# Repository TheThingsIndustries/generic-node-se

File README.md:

# Generic Node Sensor Edition (GNSE)

## About

LoRaWAN promised you roaming, secure and low-cost sensors that last on a battery for years. _Generic Node_ platform delivers this promise with additional strong end to end encryption and firmware over the air update in a device with multiple sensors that can be configured and programmed to support many use cases.

This repository contains all the necessary hardware and software files for the GNSE LoRaWAN node. The core of the system is based off the STM32WL55xx dual-core LoRaWAN SOC.

## Specification
- [STM32WL55CCU6](https://www.st.com/en/microcontrollers-microprocessors/stm32wl-series.html) dual-core Arm Cortex®-M4/M0+ @48 MHz
- 256 Kbytes of Flash & 64 Kbytes of SRAM
- SX126x sub-GHz radio
- Power output up to +22.00 dBm
- LoRa, (G)FSK, (G)MSK, BPSK modulations
- 868 MHz & 915 MHz dual-band operation
- 2xAA battery powered node with wide input voltage range: 2.2V - 5.5V
- [ATECC608A-TNGLORA](https://www.microchip.com/wwwproducts/en/ATECC608A-TNGLORA) pre-provisioned LoRaWAN secure element
- [LIS2DH12](https://www.st.com/en/mems-and-sensors/lis2dh12.html) - ULP 3-axis accelerometer
- [SHTC3](https://www.sensirion.com/en/environmental-sensors/humidity-sensors/digital-humidity-sensor-shtc3-our-new-standard-for-consumer-electronics/) humidity and temperature sensor
- [MX25R1635](https://www.macronix.com/en-us/products/NOR-Flash/Serial-NOR-Flash/Pages/default.aspx) 16Mb SPI NOR Flash for FUOTA and data-logging
- A user button, an RGB LED, a buzzer and a user-friendly expansion and programming options.

## Development

The necessary schematics and the PCB files can be found in [Hardware](./Hardware).

Software libraries and sample applications can be found in [Software](./Software).

## Documentation

The [Generic Node documentation website](https://www.genericnode.com/docs/) provides information about the node hardware and software features.

## Contribution

Our [contribution guideline](./CONTRIBUTING.md) provides more information on how to assist us with the development of GNSE.

## Legal

[Generic Node license terms and conditions](./LICENSE.md) apply.

[Contact The Things Industries](https://thethingsindustries.com/contact/) for licensing.

Copyright © 2021 The Things Industries B.V.

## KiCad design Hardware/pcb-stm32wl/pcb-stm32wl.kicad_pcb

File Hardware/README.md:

# GNSE Hardware
The reference design hardware provides the needed resources for device production, and the design can be tailored to serve a specific use case.

## Structure

- [sch](./sch/) folder contains the schematics files
- [lib](./lib/) folder contains [KiCad](https://kicad.org/) design libraries
- [pcb-stm32wl](./pcb-stm32wl/) folder contains the layout of the core STM32WL PCB
- [pcb-bolink-batteryHolder](./pcb-bolink-batteryHolder/) folder contains the layout of the bolink enclosure battery holder PCB
- [fab](./fab/) contains fabrication related files such as bill of materials(bom) and gerber files

> Please [contact The Things Industries](https://thethingsindustries.com/contact/) for the latest HW fabrication files

## Documentation

The [Generic Node documentation website](https://www.genericnode.com/docs/) provides information about the hardware features and how to [get started with the hardware development](https://www.genericnode.com/docs/getting-started/se-hw/).

## Legal
Copyright © 2021 The Things Industries B.V.

[Contact The Things Industries](https://thethingsindustries.com/contact/) for licensing.

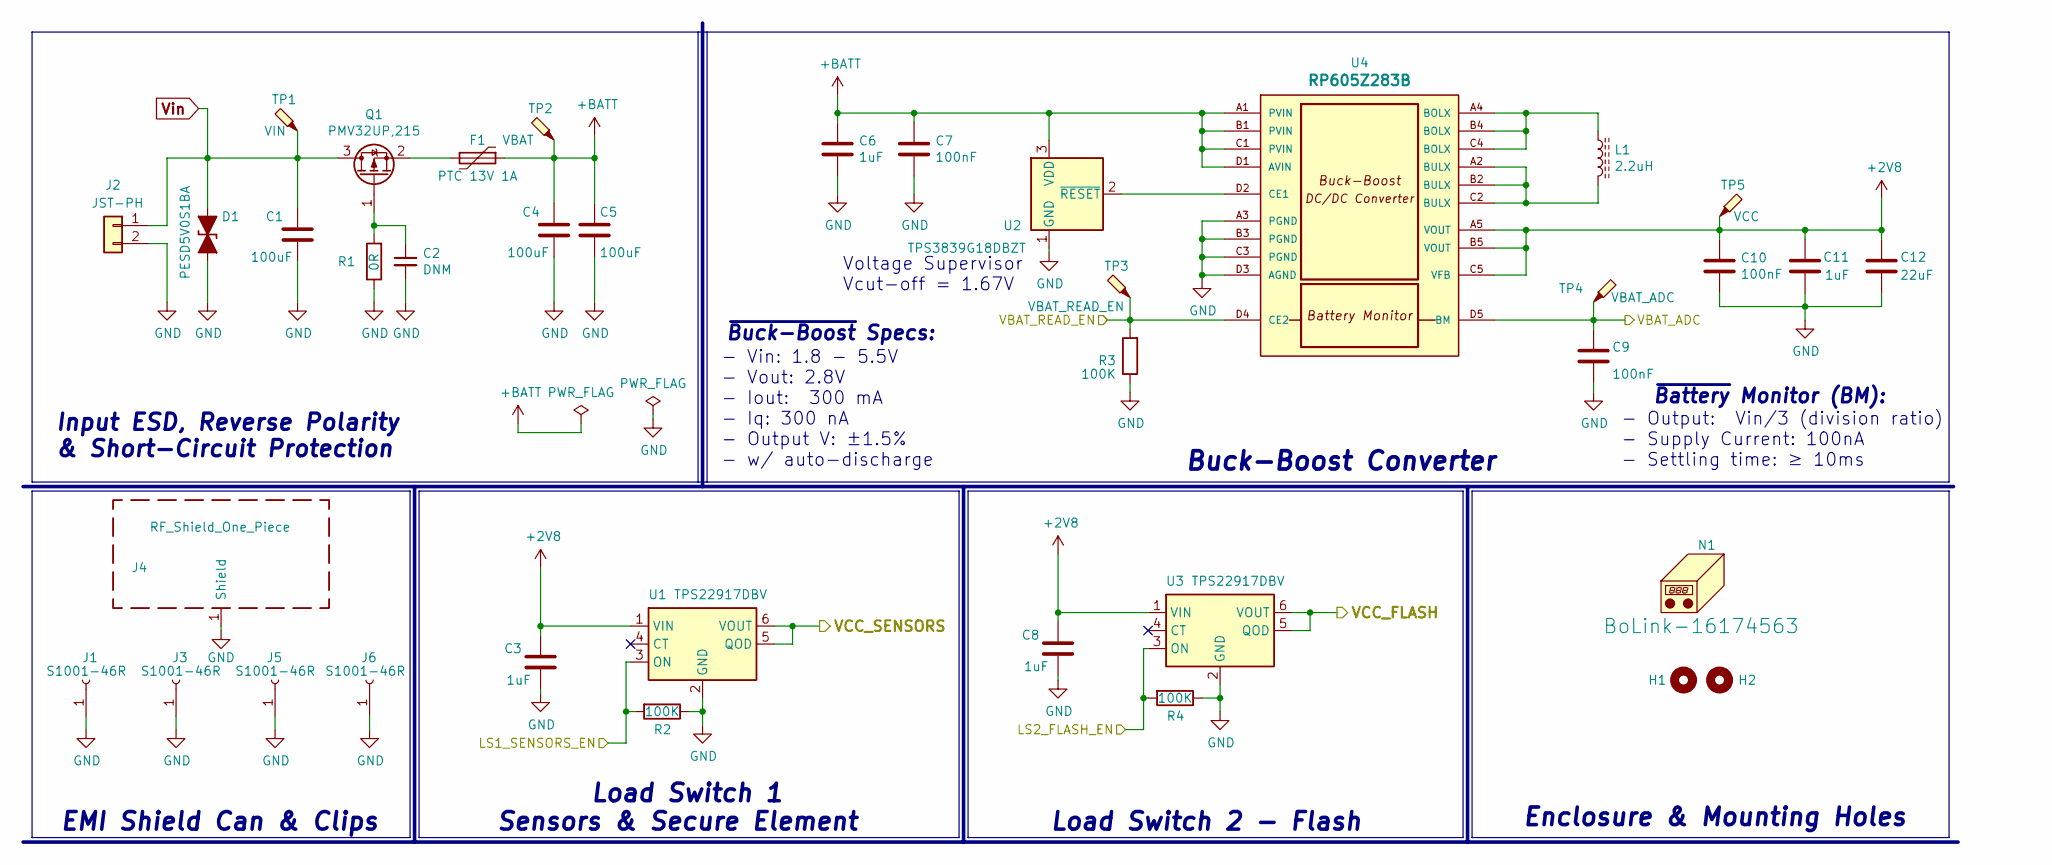
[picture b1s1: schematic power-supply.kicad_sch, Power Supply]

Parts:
C1, C4, C5: 100uF; C_1206_3216Metric; MPN JMK316ABJ107ML-T
C2: DNM; C_0402_1005Metric; MPN CC0402KRX7R7BB103
C3, C6, C8, C11: 1uF; C_0402_1005Metric; MPN CL05A105KQ5NNNC
C7, C9, C10: 100nF; C_0402_1005Metric; MPN CC0402KRX7R7BB104
C12: 22uF; C_0603_1608Metric; MPN CC0603MRX5R5BB226
D1: PESD5V0S1BA; D_SOD-323; MPN PESD5V0S1BA,115
F1: PTC 13V 1A; Fuse_1210_3225Metric_Castellated; MPN SMD1210-050
H1, H2: MountingHole; MountingHole_2.5mm
J1, J3, J5, J6: S1001-46R; RF_Shield_Clip_S1001-46R; MPN DNM
J2: JST-PH; JST_PH_B2B-PH-SM4-TB_1x02-1MP_P2.00mm_Vertical; MPN B2B-PH-SM4-TB(LF)(SN)
J4: RF_Shield_One_Piece; RF_Shield_SnapOn_30x20mm_w_Cutout_n_GND_Pads; MPN DNM
L1: 2.2uH; L_HPC4012TF-2R2M; MPN HPC4012TF-2R2M
N1: BoLink-16174563; BoLink_704025; MPN DNM
Q1: PMV32UP,215; SOT-23; MPN PMV32UP,215
R1: 0R; R_0402_1005Metric; MPN RC0402FR-070RL
R2, R3, R4: 100K; R_0402_1005Metric; MPN RC0402FR-07100KL
TP1: VIN; TestPoint_Pad_D1.5mm; MPN DNM
TP2: VBAT; TestPoint_Pad_D1.5mm; MPN DNM
TP3: VBAT_READ_EN; TestPoint_Pad_D1.5mm; MPN DNM
TP4: VBAT_ADC; TestPoint_Pad_D1.5mm; MPN DNM
TP5: VCC; TestPoint_Pad_D1.5mm; MPN DNM
U1, U3: TPS22917DBV; SOT-23-6; MPN TPS22917DBVR
U2: TPS3839G18DBZT‎; SOT-23; MPN TPS3839G18DBZT‎
U4: RP605Z283B; WLCSP-20-P3_1.994x1.609mm_Layout5x4_P0.4mm; MPN RP605Z283B-E2-F

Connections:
+BATT: C4.2, C5.2, C6.1, C7.1, F1.1, TP2.1, U2.3 (VDD), U4.A1 (PVIN), U4.B1 (PVIN), U4.C1 (PVIN), U4.D1 (AVIN)
/LoRa MCU/PB2: C9.1, TP4.1, U4.D5 (BM); also elsewhere on the board
/LoRa MCU/PB4: R3.2, TP3.1, U4.D4 (CE2); also elsewhere on the board
/Peripherals/VCC_FLASH: U3.5 (QOD), U3.6 (VOUT); also elsewhere on the board
/Peripherals/VCC_SENSORS: U1.5 (QOD), U1.6 (VOUT); also elsewhere on the board
/Power Supply/LS1_SENSORS_EN: R2.2, U1.3 (ON); also elsewhere on the board
/Power Supply/LS2_FLASH_EN: R4.2, U3.3 (ON); also elsewhere on the board
GND: C1.1, C2.2, C3.2, C4.1, C5.1, C6.2, C7.2, C8.2, C9.2, C10.1, C11.2, C12.1, D1.2 (A2), J1.1, J2.2, J3.1, J4.1, J5.1, J6.1, R1.1, R2.1, R3.1, R4.1, U1.2 (GND), U2.1 (GND), U3.2 (GND), U4.A3 (PGND), U4.B3 (PGND), U4.C3 (PGND), U4.D3 (AGND); also elsewhere on the board
unnamed: C2.1, Q1.1 (G), R1.2
unnamed: F1.2, Q1.2 (S)
unnamed: L1.1, U4.A4 (BOLX), U4.B4 (BOLX), U4.C4 (BOLX)
unnamed: L1.2, U4.A2 (BULX), U4.B2 (BULX), U4.C2 (BULX)
unnamed: U2.2 (~RESET), U4.D2 (CE1)
VDDRF: C3.1, C8.1, C10.2, C11.1, C12.2, TP5.1, U1.1 (VIN), U3.1 (VIN), U4.A5 (VOUT), U4.B5 (VOUT), U4.C5 (VFB); also elsewhere on the board
Vin: C1.2, D1.1 (A1), J2.1, Q1.3 (D), TP1.1; also elsewhere on the board

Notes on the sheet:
- Output: Vin/3 (division ratio) - Supply Current: 100nA - Settling time: ≥ 10ms
Buck-Boost Converter
EMI Shield Can & Clips
~{Buck-Boost} Specs:
- Vin: 1.8 - 5.5V - Vout: 2.8V - Iout: 300 mA - Iq: 300 nA - Output V: ±1.5% - w/ auto-discharge
Load Switch 1 Sensors & Secure Element
Load Switch 2 - Flash
Enclosure & Mounting Holes
Voltage Supervisor Vcut-off = 1.67V
~{Battery} Monitor (BM):
Input ESD, Reverse Polarity & Short-Circuit Protection

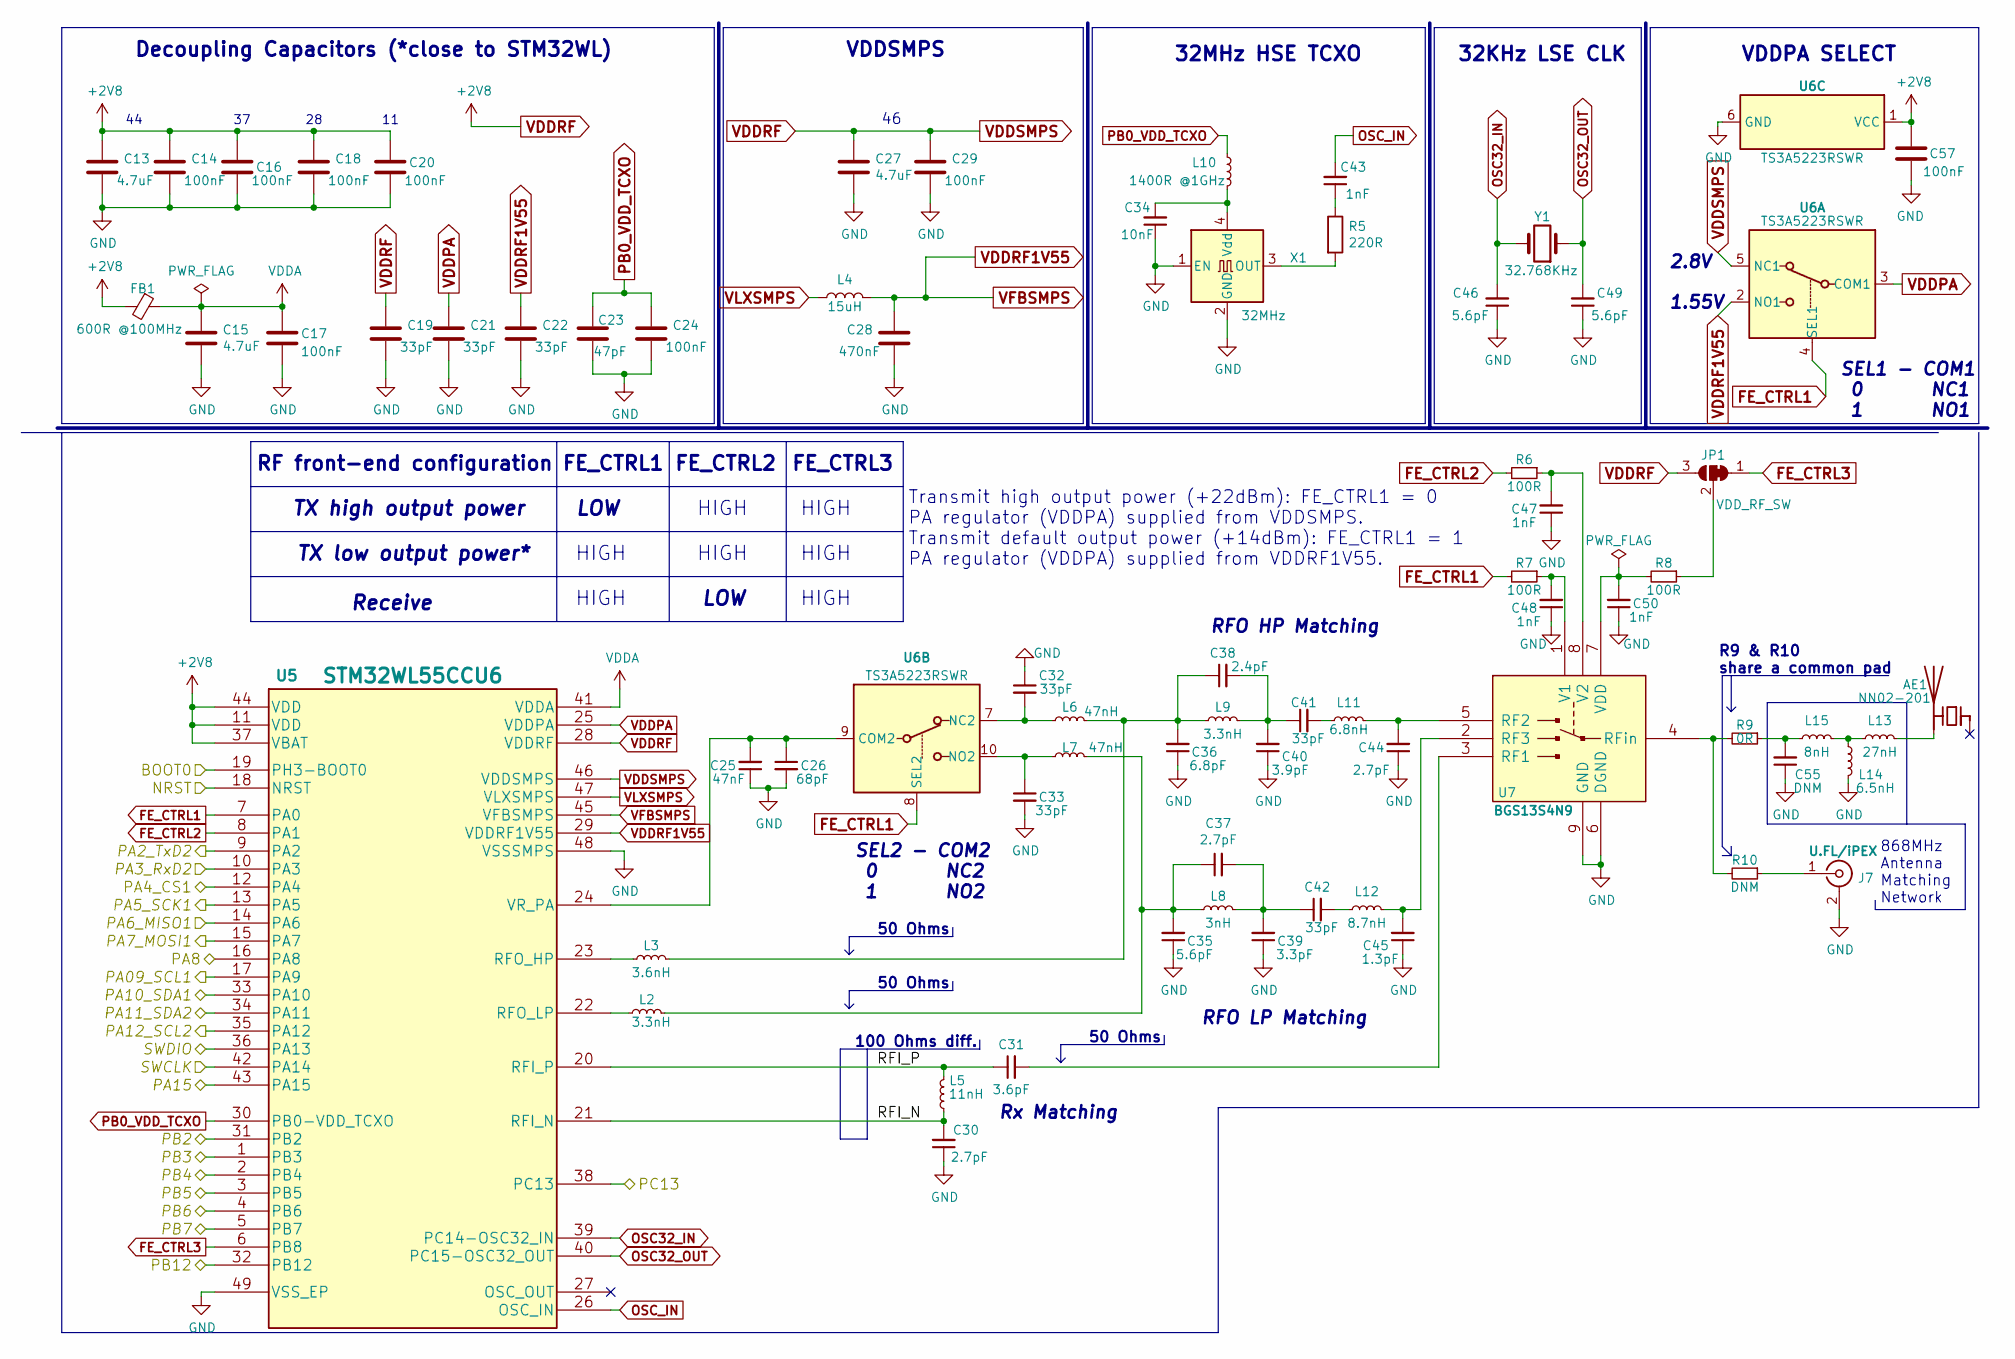
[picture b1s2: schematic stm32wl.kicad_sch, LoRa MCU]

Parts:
AE1: NN02-201; Antenna_Fractus_NN02-201; MPN NN02-201
C13, C15, C27: 4.7uF; C_0603_1608Metric; MPN CL10A475KO8NNNC
C14, C16, C17, C18, C20, C24, C29, C57: 100nF; C_0402_1005Metric; MPN CC0402KRX7R7BB104
C19, C21, C22: 33pF; C_0402_1005Metric; MPN CC0402FRNPO9BN330
C23: 47pF; C_0402_1005Metric; MPN CC0402JRNPO9BN470
C25: 47nF; C_0402_1005Metric; MPN CC0402KRX7R8BB473
C26: 68pF; C_0402_1005Metric; MPN CC0402JRNPO9BN680
C28: 470nF; C_0603_1608Metric; MPN CC0603KRX7R7BB474
C30, C37, C44: 2.7pF; C_0402_1005Metric; MPN CC0402BRNPO9BN2R7
C31: 3.6pF; C_0402_1005Metric; MPN 0402N3R6B500
C32, C33, C41, C42: 33pF; C_0402_1005Metric; MPN CC0402GRNPO9BN330
C34: 10nF; C_0402_1005Metric; MPN CC0402KRX7R7BB103
C35, C46, C49: 5.6pF; C_0402_1005Metric; MPN CC0402BRNPO9BN5R6
C36: 6.8pF; C_0402_1005Metric; MPN CC0402BRNPO9BN6R8
C38: 2.4pF; C_0402_1005Metric; MPN CC0402BRNPO9BN2R4
C39: 3.3pF; C_0402_1005Metric; MPN CC0402BRNPO9BN3R3
C40: 3.9pF; C_0402_1005Metric; MPN CC0402BRNPO9BN3R9
C43, C47, C48, C50: 1nF; C_0402_1005Metric; MPN CC0402KRX7R7BB102
C45: 1.3pF; C_0402_1005Metric; MPN CC0402BRNPO9BN1R3
C55: DNM; C_0402_1005Metric; MPN DNM
FB1: 600R @100MHz; L_0603_1608Metric; MPN BLM18AG601SN1D
J7: U.FL/iPEX; U.FL_Hirose_U.FL-R-SMT-1_Vertical; MPN U.FL-R-SMT-1(10)
JP1: VDD_RF_SW; SolderJumper-3_P1.3mm_Bridged12_RoundedPad1.0x1.5mm_NumberL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
L2, L9: 3.3nH; L_0402_1005Metric; MPN LQW15AN3N3C80D
L3: 3.6nH; L_0402_1005Metric; MPN LQW15AN3N6C10D
L4: 15uH; L_0805_2012Metric_custom; MPN MLZ2012M150W
L5: 11nH; L_0402_1005Metric; MPN LQW15AN11NG00
L6, L7: 47nH; L_0402_1005Metric; MPN LQW15AN47NJ00#
L8: 3nH; L_0402_1005Metric; MPN LQW15AN3N0B00
L10: 1400R @1GHz; L_0402_1005Metric; MPN BLM15HG102SN1D
L11: 6.8nH; L_0402_1005Metric; MPN LQW15AN6N8H00
L12: 8.7nH; L_0402_1005Metric; MPN LQW15AN8N7H00
L13: 27nH; L_0402_1005Metric; MPN LQW15AN27NG00
L14: 6.5nH; L_0402_1005Metric; MPN LQW15AN6N5G80
L15: 8nH; L_0402_1005Metric; MPN LQW15AN8N0G80
R5: 220R; L_0402_1005Metric; MPN RC0402FR-07220RL
R6, R7, R8: 100R; R_0402_1005Metric; MPN RC0402FR-07100RL
R9: 0R; R_0402_1005Metric; MPN RC0402FR-070RL
R10: DNM; R_0402_1005Metric; MPN DNM
U5: STM32WL55CCU6; QFN-48-1EP_7x7mm_P0.5mm_EP5.45x5.45mm; MPN STM32WL55CCU6
U6: TS3A5223RSWR; UQFN-10_1.4x1.8mm_P0.4mm; MPN TS3A5223RSWR
U7: BGS13S4N9; RFSW_BGS13S4N9E6327XTSA1; MPN BGS13S4N9E6327XTSA1
X1: 32MHz; Crystal_SMD_Abracon_ABM10-4Pin_2.5x2.0mm; MPN ‎TG2520SMN 32.0000M-MCGNNM3‎
Y1: 32.768KHz; Crystal_SMD_NX2012SA_32.768KHz; MPN X1A000061002100

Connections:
/LoRa MCU/BOOT0: U5.19 (PH3-BOOT0); also elsewhere on the board
/LoRa MCU/NRST: U5.18 (NRST); also elsewhere on the board
/LoRa MCU/PA2_TxD2: U5.9 (PA2); also elsewhere on the board
/LoRa MCU/PA3_RxD2: U5.10 (PA3); also elsewhere on the board
/LoRa MCU/PA5_SCK1: U5.13 (PA5); also elsewhere on the board
/LoRa MCU/PA8: U5.16 (PA8); also elsewhere on the board
/LoRa MCU/PA09_SCL1: U5.17 (PA9); also elsewhere on the board
/LoRa MCU/PA10_SDA1: U5.33 (PA10); also elsewhere on the board
/LoRa MCU/PA11_SDA2: U5.34 (PA11); also elsewhere on the board
/LoRa MCU/PA12_SCL2: U5.35 (PA12); also elsewhere on the board
/LoRa MCU/PA15: U5.43 (PA15); also elsewhere on the board
/LoRa MCU/PB2: U5.31 (PB2); also elsewhere on the board
/LoRa MCU/PB3: U5.1 (PB3); also elsewhere on the board
/LoRa MCU/PB4: U5.2 (PB4); also elsewhere on the board
/LoRa MCU/PB5: U5.3 (PB5); also elsewhere on the board
/LoRa MCU/PB6: U5.4 (PB6); also elsewhere on the board
/LoRa MCU/PB7: U5.5 (PB7); also elsewhere on the board
/LoRa MCU/RFI_N: C30.2, L5.1, U5.21 (RFI_N)
/LoRa MCU/RFI_P: C31.1, L5.2, U5.20 (RFI_P)
/LoRa MCU/SWCLK: U5.42 (PA14); also elsewhere on the board
/LoRa MCU/SWDIO: U5.36 (PA13); also elsewhere on the board
/Peripherals/FlashCS: U5.12 (PA4); also elsewhere on the board
/Peripherals/MISO: U5.14 (PA6); also elsewhere on the board
/Peripherals/MOSI: U5.15 (PA7); also elsewhere on the board
/Power Supply/LS1_SENSORS_EN: U5.32 (PB12); also elsewhere on the board
/Power Supply/LS2_FLASH_EN: U5.38 (PC13); also elsewhere on the board
FE_CTRL1: R7.2, U5.7 (PA0), U6.4 (SEL1), U6.8 (SEL2)
FE_CTRL2: R6.2, U5.8 (PA1)
FE_CTRL3: JP1.1 (A), U5.6 (PB8)
GND: C13.2, C14.2, C15.2, C16.2, C17.2, C18.2, C19.2, C20.2, C21.2, C22.2, C23.2, C24.2, C25.1, C26.2, C27.2, C28.2, C29.2, C30.1, C32.1, C33.2, C34.1, C35.1, C36.1, C39.1, C40.1, C44.1, C45.1, C46.1, C47.1, C48.1, C49.1, C50.1, C55.1, C57.2, J7.2 (Ext), L14.1, U5.48 (VSSSMPS), U5.49 (VSS_EP), U6.6 (GND), U7.6 (DGND), U7.9 (GND), X1.1 (EN), X1.2 (GND); also elsewhere on the board
unnamed: AE1.2 (PCB_Trace), L13.2
unnamed: C25.2, C26.1, U5.24 (VR_PA), U6.9 (COM2)
unnamed: C31.2, U7.3 (RF1)
unnamed: C32.2, L6.1, U6.7 (NC2)
unnamed: C33.1, L7.1, U6.10 (NO2)
unnamed: C34.2, L10.2, X1.4 (Vdd)
unnamed: C35.2, C37.1, L2.2, L7.2, L8.1
unnamed: C36.2, C38.1, L3.2, L6.2, L9.1
unnamed: C37.2, C39.2, C42.1, L8.2
unnamed: C38.2, C40.2, C41.1, L9.2
unnamed: C41.2, L11.1
unnamed: C42.2, L12.1
unnamed: C43.1, R5.1
unnamed: C44.2, L11.2, U7.5 (RF2)
unnamed: C45.2, L12.2, U7.2 (RF3)
unnamed: C47.2, R6.1, U7.8 (V2)
unnamed: C48.2, R7.1, U7.1 (V1)
unnamed: C50.2, R8.2, U7.7 (VDD)
unnamed: C55.2, L15.1, R9.1
unnamed: J7.1 (In), R10.1
unnamed: JP1.2 (C), R8.1
unnamed: L2.1, U5.22 (RFO_LP)
unnamed: L3.1, U5.23 (RFO_HP)
unnamed: L13.1, L14.2, L15.2
unnamed: R5.2, X1.3 (OUT)
unnamed: R9.2, R10.2, U7.4 (RFin)
OSC32_IN: C46.2, U5.39 (PC14-OSC32_IN), Y1.2
OSC32_OUT: C49.2, U5.40 (PC15-OSC32_OUT), Y1.1
OSC_IN: C43.2, U5.26 (OSC_IN)
PB0_VDD_TCXO: C23.1, C24.1, L10.1, U5.30 (PB0-VDD_TCXO)
VDDA: C15.1, C17.1, FB1.1, U5.41 (VDDA)
VDDPA: C21.1, U5.25 (VDDPA), U6.3 (COM1)
VDDRF: C13.1, C14.1, C16.1, C18.1, C19.1, C20.1, C27.1, C29.1, C57.1, FB1.2, JP1.3 (B), U5.11 (VDD), U5.28 (VDDRF), U5.37 (VBAT), U5.44 (VDD), U5.46 (VDDSMPS), U6.1 (VCC), U6.5 (NC1); also elsewhere on the board
VDDRF1V55: C22.1, C28.1, L4.2, U5.29 (VDDRF1V55), U5.45 (VFBSMPS), U6.2 (NO1)
VLXSMPS: L4.1, U5.47 (VLXSMPS)

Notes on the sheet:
HIGH
Decoupling Capacitors (*close to STM32WL)
LOW
Receive
TX low output power*
100 Ohms diff.
SEL2 - COM2 0 NC2 1 NO2
FE_CTRL3
50 Ohms
FE_CTRL1
TX high output power
32MHz HSE TCXO
SEL1 - COM1 0 NC1 1 NO1
RFO LP Matching
Rx Matching
VDDSMPS
Transmit high output power (+22dBm): FE_CTRL1 = 0 PA regulator (VDDPA) supplied from VDDSMPS. Transmit default output power (+14dBm): FE_CTRL1 = 1 PA regulator (VDDPA) supplied from VDDRF1V55.
FE_CTRL2
2.8V
32KHz LSE CLK
RF front-end configuration
RFO HP Matching
R9 & R10 share a common pad
868MHz Antenna Matching Network
VDDPA SELECT
1.55V

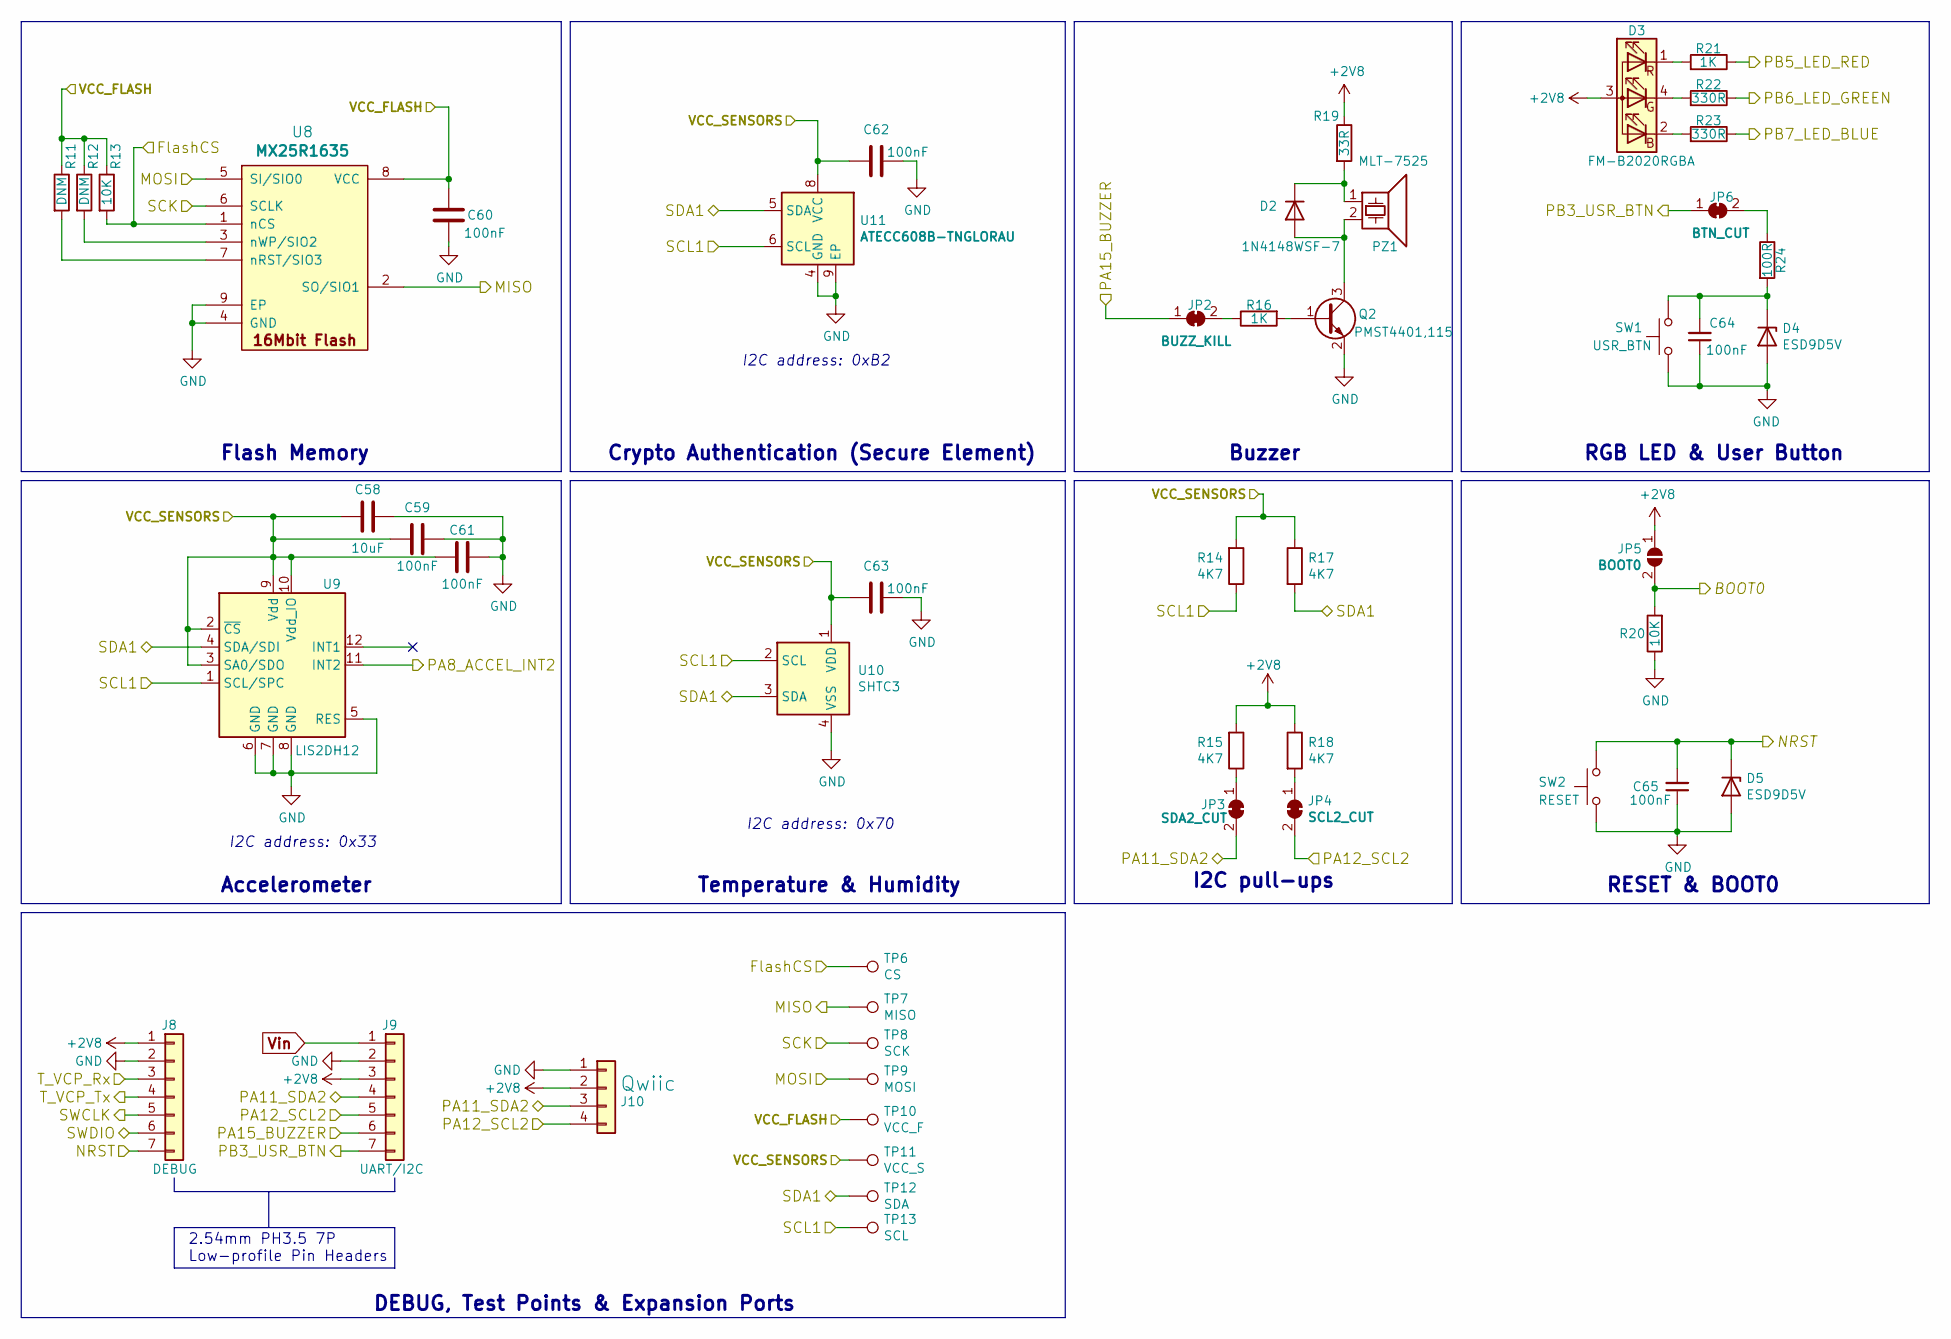
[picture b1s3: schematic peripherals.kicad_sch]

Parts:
C58: 10uF; C_0603_1608Metric; MPN JMK107ABJ106KA-T
C59, C60, C61, C62, C63, C64, C65: 100nF; C_0402_1005Metric; MPN CC0402KRX7R7BB104
D2: 1N4148WSF-7; D_SOD-323F_custom; MPN 1N4148WSF-7
D3: FM-B2020RGBA; LED_Cree-PLCC4_2x2mm_CW; MPN FM-B2020RGBA-HG
D4, D5: ESD9D5V; D_SOD-923; MPN Diode_SMD:D_SOD-923
J8: DEBUG; PinSocket_1x07_P2.54mm_Vertical
J9: UART/I2C; PinSocket_1x07_P2.54mm_Vertical
J10: Qwiic; JST_SH_BM04B-SRSS-TB_1x04-1MP_P1.00mm_Vertical; MPN BM04B-SRSS-TB(LF)(SN)
JP2: BUZZ_KILL; SolderJumper-2_P1.3mm_Bridged2Bar_RoundedPad1.0x1.5mm
JP3: SDA2_CUT; SolderJumper-2_P1.3mm_Bridged2Bar_RoundedPad1.0x1.5mm
JP4: SCL2_CUT; SolderJumper-2_P1.3mm_Bridged2Bar_RoundedPad1.0x1.5mm
JP5: BOOT0; PinHeader_1x02_P1.27mm_Vertical
JP6: BTN_CUT; SolderJumper-2_P1.3mm_Bridged2Bar_RoundedPad1.0x1.5mm
PZ1: MLT-7525; Buzzer_MLT-7525; MPN MLT-7525
Q2: PMST4401,115; SOT-323_SC-70; MPN PMST4401,115
R11, R12: DNM; R_0402_1005Metric; MPN DNM
R13: 10K; R_0402_1005Metric; MPN AC0402JR-0710KL
R14, R15, R17, R18: 4K7; R_0402_1005Metric; MPN AC0402FR-074K7L
R16, R21: 1K; R_0402_1005Metric; MPN RC0402FR-071KL
R19: 33R; R_0402_1005Metric; MPN AC0402JR-0733RL
R20: 10K; L_0402_1005Metric; MPN AC0402JR-0710KL
R22, R23: 330R; R_0402_1005Metric; MPN AC0402FR-07330RL
R24: 100R; R_0402_1005Metric; MPN RC0402FR-07100RL
SW1: USR_BTN; PushButton_KSC721GLFS; MPN KSC721GLFS
SW2: RESET; SW_SPST_SKSHABE010; MPN SKSHABE010
TP6: CS; TestPoint_Pad_D1.5mm; MPN DNM
TP7: MISO; TestPoint_Pad_D1.5mm; MPN DNM
TP8: SCK; TestPoint_Pad_D1.5mm; MPN DNM
TP9: MOSI; TestPoint_Pad_D1.5mm; MPN DNM
TP10: VCC_F; TestPoint_Pad_D1.5mm; MPN DNM
TP11: VCC_S; TestPoint_Pad_D1.5mm; MPN DNM
TP12: SDA; TestPoint_Pad_D1.5mm; MPN DNM
TP13: SCL; TestPoint_Pad_D1.5mm; MPN DNM
U8: MX25R1635; FLASH_UFDFN-8-MX25R1635F; MPN MX25R1635FZUIL0
U9: LIS2DH12; LGA-12_2x2mm_P0.5mm; MPN LIS2DH12TR
U10: SHTC3; Sensirion_DFN-4-1EP_2x2mm_P1mm_EP0.7x1.6mm; MPN SHTC3
U11: ATECC608B-TNGLORAU; DFN-8-1EP_3x2mm_P0.5mm_EP1.3x1.5mm; MPN ATECC608B-TNGLORAU-C

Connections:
/LoRa MCU/BOOT0: JP5.2 (B), R20.2; also elsewhere on the board
/LoRa MCU/NRST: C65.2, D5.1 (K), J8.7, SW2.2; also elsewhere on the board
/LoRa MCU/PA2_TxD2: J8.4; also elsewhere on the board
/LoRa MCU/PA3_RxD2: J8.3; also elsewhere on the board
/LoRa MCU/PA5_SCK1: TP8.1, U8.6 (SCLK); also elsewhere on the board
/LoRa MCU/PA8: U9.11 (INT2); also elsewhere on the board
/LoRa MCU/PA09_SCL1: R14.1, TP13.1, U9.1 (SCL/SPC), U10.2 (SCL), U11.6 (SCL); also elsewhere on the board
/LoRa MCU/PA10_SDA1: R17.2, TP12.1, U9.4 (SDA/SDI), U10.3 (SDA), U11.5 (SDA); also elsewhere on the board
/LoRa MCU/PA11_SDA2: J9.4, J10.3, JP3.2 (B); also elsewhere on the board
/LoRa MCU/PA12_SCL2: J9.5, J10.4, JP4.2 (B); also elsewhere on the board
/LoRa MCU/PA15: J9.6, JP2.1 (A); also elsewhere on the board
/LoRa MCU/PB3: J9.7, JP6.1 (A); also elsewhere on the board
/LoRa MCU/PB5: R21.1; also elsewhere on the board
/LoRa MCU/PB6: R22.1; also elsewhere on the board
/LoRa MCU/PB7: R23.1; also elsewhere on the board
/LoRa MCU/SWCLK: J8.5; also elsewhere on the board
/LoRa MCU/SWDIO: J8.6; also elsewhere on the board
/Peripherals/FlashCS: R13.2, TP6.1, U8.1 (nCS); also elsewhere on the board
/Peripherals/MISO: TP7.1, U8.2 (SO/SIO1); also elsewhere on the board
/Peripherals/MOSI: TP9.1, U8.5 (SI/SIO0); also elsewhere on the board
/Peripherals/VCC_FLASH: C60.2, R11.1, R12.1, R13.1, TP10.1, U8.8 (VCC); also elsewhere on the board
/Peripherals/VCC_SENSORS: C58.2, C59.2, C61.2, C62.2, C63.2, R14.2, R17.1, TP11.1, U9.2 (~CS), U9.3 (SA0/SDO), U9.9 (Vdd), U9.10 (Vdd_IO), U10.1 (VDD), U11.8 (VCC); also elsewhere on the board
GND: C58.1, C59.1, C60.1, C61.1, C62.1, C63.1, C64.1, C65.1, D4.2 (A), D5.2 (A), J8.2, J9.2, J10.1, Q2.2 (E), R20.1, SW1.2, SW2.1, U8.4 (GND), U8.9 (EP), U9.5 (RES), U9.6 (GND), U9.7 (GND), U9.8 (GND), U10.4 (VSS), U11.4 (GND), U11.9 (EP); also elsewhere on the board
unnamed: C64.2, D4.1 (K), R24.2, SW1.1
unnamed: D2.1 (K), PZ1.1, R19.2
unnamed: D2.2 (A), PZ1.2, Q2.3 (C)
unnamed: D3.1 (RK), R21.2
unnamed: D3.2 (GK), R23.2
unnamed: D3.4 (A), R22.2
unnamed: JP2.2 (B), R16.1
unnamed: JP3.1 (A), R15.1
unnamed: JP4.1 (A), R18.2
unnamed: JP6.2 (B), R24.1
unnamed: Q2.1 (B), R16.2
unnamed: R11.2, U8.7 (nRST/SIO3)
unnamed: R12.2, U8.3 (nWP/SIO2)
VDDRF: D3.3 (BK), J8.1, J9.3, J10.2, JP5.1 (A), R15.2, R18.1, R19.1; also elsewhere on the board
Vin: J9.1; also elsewhere on the board

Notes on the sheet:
I2C pull-ups
Flash Memory
Buzzer
2.54mm PH3.5 7P Low-profile Pin Headers
Temperature & Humidity
Crypto Authentication (Secure Element)
I2C address: 0xB2
I2C address: 0x70
Accelerometer
RESET & BOOT0
DEBUG, Test Points & Expansion Ports
RGB LED & User Button
I2C address: 0x33

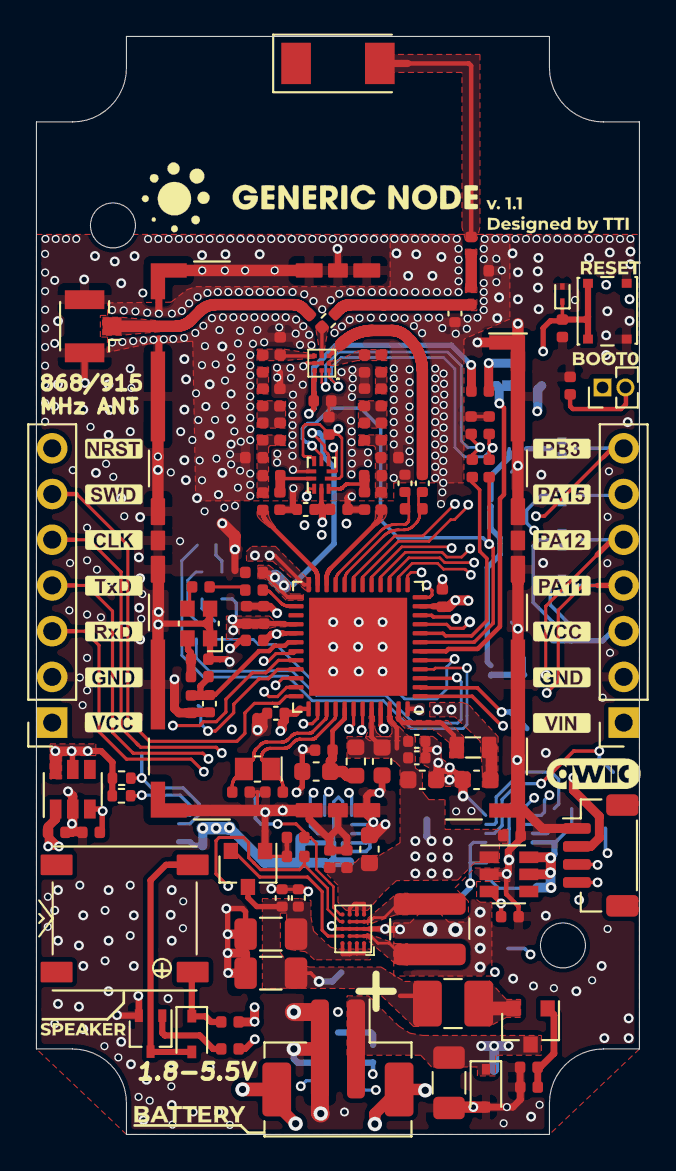
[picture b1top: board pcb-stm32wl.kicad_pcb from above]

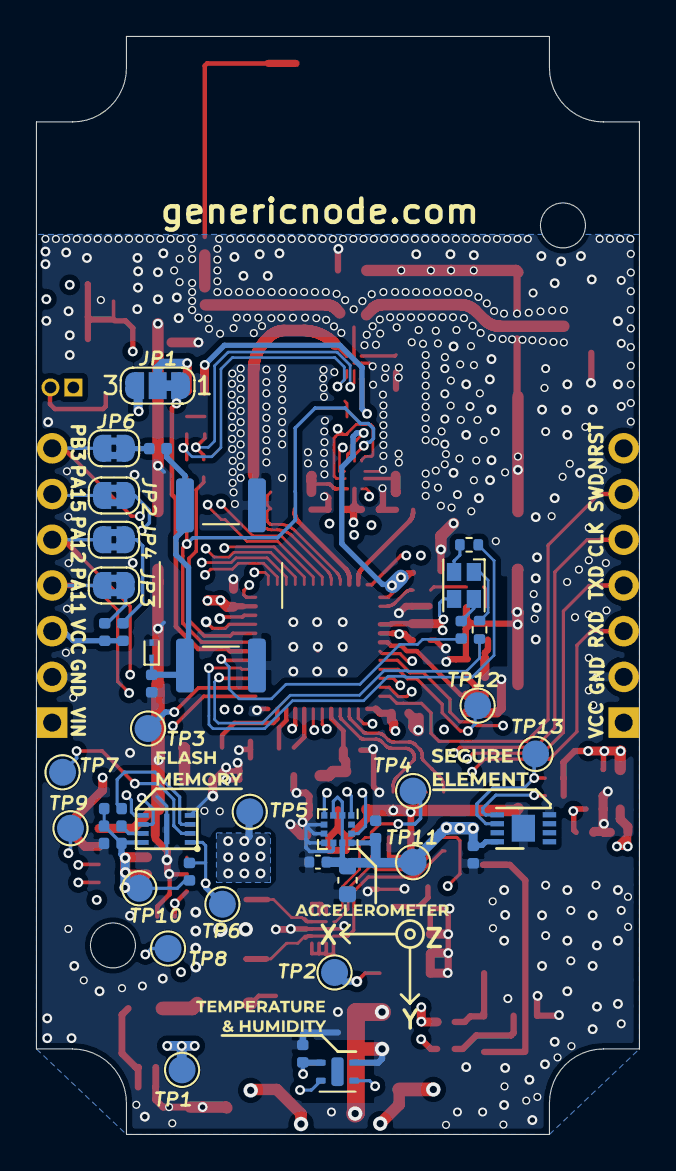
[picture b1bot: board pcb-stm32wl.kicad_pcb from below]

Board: 4 copper layers, 33.5 x 61.0 mm, 182 parts (45 on the bottom side), 87 nets.

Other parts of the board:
G-ACCELL: LOGO; LAbel_ACCELL_2000px
G-BAT: LOGO; Label_BATTERY_2500px
G-BOOT0: LOGO; Label_BOOT0_4000px
G-CLK: LOGO; PinName_CLK
G-FLASH: LOGO; Label_FLASH_3000px
G-GND, G-GND2: LOGO; PinName_GND
G-GNSE: LOGO; Logo_GN_new_2000px
G-NRST: LOGO; PinName_NRST
G-PA11: LOGO; PinName_PA11
G-PA12: LOGO; PinName_PA12
G-PA15: LOGO; PinName_PA15
G-PB3: LOGO; PinName_PB3
G-QWIIC: LOGO; Logo_qwiic_4000px
G-RST: LOGO; Label_RESET_4000px
G-RXD: LOGO; PinName_RxD
G-SE: LOGO; Label_SE_3000px
G-SPKR: LOGO; Label_Speaker
G-SWD: LOGO; PinName_SWD
G-TH: LOGO; Label_T_H_2000px
G-TXD: LOGO; PinName_TxD
G-VCC, G-VCC2: LOGO; PinName_VCC
G-VIN: LOGO; PinName_VIN
G-version: LOGO; Logo_design_version_2000px

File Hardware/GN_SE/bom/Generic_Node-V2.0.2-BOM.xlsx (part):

Item | Reference | Quantity | Value | MPN | ALT_MPN | Footprint | URL
1 | AE1 | 1 | NN02-201 | NN02-201 |  | node-lib-v1:Antenna_Fractus_NN02-201 | https://www.digikey.nl/short/zdc4q9
2 | C12 | 1 | 22uF | CC0603MRX5R5BB226 | JMK107BBJ226MA | Capacitor_SMD:C_0603_1608Metric | https://lcsc.com/product-detail/Multilayer-Ceramic-Capacitor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
3 | C13 C15 C27 | 3 | 4.7uF | CL10A475KO8NNNC | C1608X5R1C475K080AC | Capacitor_SMD:C_0603_1608Metric | https://lcsc.com/product-detail/Multilayer-Ceramic-Capacitor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
4 | C2 C34 | 2 | 10nF | CC0402KRX7R7BB103 |  | Capacitor_SMD:C_0402_1005Metric | https://lcsc.com/product-detail/Multilayer-Ceramic-Capacitor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
5 | C23 | 1 | 47pF | CC0402JRNPO9BN470 |  | Capacitor_SMD:C_0402_1005Metric | https://lcsc.com/product-detail/Multilayer-Ceramic-Capacitor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
6 | C25 | 1 | 47nF | CC0402KRX7R8BB473 |  | Capacitor_SMD:C_0402_1005Metric | https://lcsc.com/product-detail/Multilayer-Ceramic-Capacitor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
7 | C26 | 1 | 68pF | CC0402JRNPO9BN680 |  | Capacitor_SMD:C_0402_1005Metric | https://lcsc.com/product-detail/Multilayer-Ceramic-Capacitor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
8 | C28 | 1 | 470nF | CC0603KRX7R7BB474 |  | Capacitor_SMD:C_0603_1608Metric | https://lcsc.com/product-detail/Multilayer-Ceramic-Capacitor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
9 | C30 C37 C44 | 3 | 2.7pF | CC0402BRNPO9BN2R7 |  | Capacitor_SMD:C_0402_1005Metric | https://lcsc.com/product-detail/Multilayer-Ceramic-Capacitor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
10 | C31 | 1 | 3.6pF | 0402N3R6B500 | CC0402BRNPO9BN3R6 | Capacitor_SMD:C_0402_1005Metric | https://lcsc.com/product-detail/Multilayer-Ceramic-Capacitor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
11 | C19 C21 C22 C32 C33 C41 C42 | 7 | 33pF | CC0402GRNPO9BN330 |  | Capacitor_SMD:C_0402_1005Metric | https://lcsc.com/product-detail/Multilayer-Ceramic-Capacitor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
12 | C35 C46 C49 | 3 | 5.6pF | CC0402BRNPO9BN5R6 |  | Capacitor_SMD:C_0402_1005Metric | https://lcsc.com/product-detail/Multilayer-Ceramic-Capacitor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
13 | C36 | 1 | 6.8pF | CC0402BRNPO9BN6R8 |  | Capacitor_SMD:C_0402_1005Metric | https://lcsc.com/product-detail/Multilayer-Ceramic-Capacitor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
14 | C38 | 1 | 2.4pF | CC0402BRNPO9BN2R4 |  | Capacitor_SMD:C_0402_1005Metric | https://lcsc.com/product-detail/Multilayer-Ceramic-Capacitor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
15 | C39 C54 | 2 | 3.3pF | CC0402BRNPO9BN3R3 | GJM1555C1H3R3WB01 | Capacitor_SMD:C_0402_1005Metric | https://lcsc.com/product-detail/Multilayer-Ceramic-Capacitor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
16 | C1 C4 C5 | 3 | 100uF | JMK316ABJ107ML-T |  | Capacitor_SMD:C_1206_3216Metric | https://lcsc.com/product-detail/Multilayer-Ceramic-Capacitor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
17 | C40 | 1 | 3.9pF | CC0402BRNPO9BN3R9 |  | Capacitor_SMD:C_0402_1005Metric | https://lcsc.com/product-detail/Multilayer-Ceramic-Capacitor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
18 | C45 | 1 | 1.3pF | CC0402BRNPO9BN1R3 |  | Capacitor_SMD:C_0402_1005Metric | https://lcsc.com/product-detail/Multilayer-Ceramic-Capacitor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
19 | C43 C47 C48 C50 | 4 | 1nF | CC0402KRX7R7BB102 |  | Capacitor_SMD:C_0402_1005Metric | https://lcsc.com/product-detail/Multilayer-Ceramic-Capacitor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
20 | C55 |  | DNM | DNM | CC0402BRNPO9BN3R3 | Capacitor_SMD:C_0402_1005Metric | https://lcsc.com/product-detail/Multilayer-Ceramic-Capacitor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
21 | C58 | 1 | 10uF | JMK107ABJ106KA-T | C1608X5R0J106K080AB | Capacitor_SMD:C_0603_1608Metric | https://lcsc.com/product-detail/Others_Taiyo-Yuden_JMK107ABJ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
22 | C3 C6 C8 C11 | 4 | 1uF | CL05A105KQ5NNNC |  | Capacitor_SMD:C_0402_1005Metric | https://lcsc.com/product-detail/Multilayer-Ceramic-Capacitor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
23 | C7 C9 C10 C14 C16 C17 C18 C20 C24 C29 C57 C59 C60 C61 C62 C63 C64 C65 | 18 | 100nF | CC0402KRX7R7BB104 |  | Capacitor_SMD:C_0402_1005Metric | https://lcsc.com/product-detail/Multilayer-Ceramic-Capacitor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
24 | D1 | 1 | PESD5V0S1BA | PESD5V0S1BA,115 |  | Diode_SMD:D_SOD-323 | https://lcsc.com/product-detail/TVS_Nexperia-PESD5V0S1BA-115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
25 | D2 | 1 | 1N4148WSF-7 | 1N4148WSF-7 |  | Diode_SMD:D_SOD-323F | https://lcsc.com/product-detail/Switching-Diode_Diodes-Incor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
26 | D3 | 1 | FM-B2020RGBA | FM-B2020RGBA-HG |  | LED_SMD:LED_Cree-PLCC4_2x2mm_CW | https://lcsc.com/product-detail/Light-Emitting-Diodes-LED_Fo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
27 | D4 D5 | 2 | ESD9D5V | Diode_SMD:D_SOD-923 |  | Diode_SMD:D_SOD-923 | https://lcsc.com/product-detail/TVS_Leiditech-ESD9D5V_C384848.html
28 | F1 | 1 | PTC 13V 1A | SMD1210-050 |  | Fuse:Fuse_1210_3225Metric_Castellated | https://lcsc.com/product-detail/PTC-Resettable-Fuses_TECHFUS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
29 | FB1 | 1 | 600R @100MHz | BLM18AG601SN1D |  | Inductor_SMD:L_0603_1608Metric | https://lcsc.com/product-detail/Ferrite-Beads_Murata-Electro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
30 | FID1 FID2 FID3 FID4 FID5 FID6 | 6 | Fiducial | ~ |  | Fiducial:Fiducial_0.5mm_Mask1.5mm | ~
31 | H1 H2 | 2 | MountingHole | ~ |  | MountingHole:MountingHole_2.5mm | ~
32 | J1 J3 J5 J6 |  | S1001-46R | DNM | S1001-46R | node-lib-v1:RF_Shield_Clip_S1001-46R | https://www.digikey.com/short/zwbq0r
33 | J10 | 1 | Qwiic | BM04B-SRSS-TB(LF)(SN) |  | Connector_JST:JST_SH_BM04B-SRSS-TB_1x04-1MP_P1.00mm_Vertical | https://lcsc.com/product-detail/Wire-To-Board-Wire-To-Wire-C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
34 | J2 | 1 | JST-PH | B2B-PH-SM4-TB(LF)(SN) |  | Connector_JST:JST_PH_B2B-PH-SM4-TB_1x02-1MP_P2.00mm_Vertical | https://lcsc.com/product-detail/Wire-To-Board-Wire-To-Wire-C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
35 | J4 |  | RF_Shield_One_Piece | DNM | S02-30200250 | node-lib-v1:Harwin_S02-30200250_30x20mm_GND_Pads | https://www.digikey.com/short/zwbq0z
36 | J7 | 1 | U.FL/iPEX | U.FL-R-SMT-1(10) |  | Connector_Coaxial:U.FL_Hirose_U.FL-R-SMT-1_Vertical | https://lcsc.com/product-detail/RF-Connectors-Coaxial-Connec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
37 | J8 |  | DEBUG | DNM | C124418 | Connector_PinSocket_2.54mm:PinSocket_1x07_P2.54mm_Vertical | https://lcsc.com/product-detail/Pin-Header-Female-Header_Ckm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
38 | J9 |  | UART/I2C | DNM | C124418 | Connector_PinSocket_2.54mm:PinSocket_1x07_P2.54mm_Vertical | https://lcsc.com/product-detail/Pin-Header-Female-Header_Ckm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
39 | JP1 | 1 | VDD_RF_SW | ~ |  | Jumper:SolderJumper-3_P1.3mm_Bridged12_RoundedPad1.0x1.5mm_NumberLabels | ~
40 | JP2 | 1 | BUZZ_KILL | ~ |  | Jumper:SolderJumper-2_P1.3mm_Bridged2Bar_RoundedPad1.0x1.5mm | ~
41 | JP3 | 1 | SDA2_CUT | ~ |  | Jumper:SolderJumper-2_P1.3mm_Bridged2Bar_RoundedPad1.0x1.5mm | ~
42 | JP4 | 1 | SCL2_CUT | ~ |  | Jumper:SolderJumper-2_P1.3mm_Bridged2Bar_RoundedPad1.0x1.5mm | ~
43 | JP5 | 1 | BOOT0 | ~ |  | Connector_PinHeader_1.27mm:PinHeader_1x02_P1.27mm_Vertical | ~
44 | JP6 | 1 | BTN_CUT | ~ |  | Jumper:SolderJumper-2_P1.3mm_Bridged2Bar_RoundedPad1.0x1.5mm | ~
45 | L1 | 1 | 2.2uH | HPC4012TF-2R2M |  | node-lib-v1:L_HPC4012TF-2R2M | https://lcsc.com/product-detail/Power-Inductors_TAI-TECH-HPC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
46 | L10 | 1 | 1400R @1GHz | BLM15HG102SN1D |  | Inductor_SMD:L_0402_1005Metric | https://lcsc.com/product-detail/Ferrite-Beads_Murata-Electro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
47 | L11 | 1 | 6.8nH | LQW15AN6N8H00 |  | Inductor_SMD:L_0402_1005Metric | https://www.digikey.com/short/zwbq90
48 | L12 | 1 | 8.7nH | LQW15AN8N7H00 |  | Inductor_SMD:L_0402_1005Metric | https://www.digikey.com/short/zwbq9f
49 | L13 | 1 | 23nH | LQW18AN23NG80 |  | Inductor_SMD:L_0402_1005Metric | https://eu.mouser.com/ProductDetail/Murata-Electronics/LQW18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
50 | L14 | 1 | 4.3nH | LQW15AN4N3G80 |  | Inductor_SMD:L_0402_1005Metric | https://lcsc.com/product-detail/Inductors-SMD_Murata-Electro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
51 | L3 | 1 | 3.6nH | LQW15AN3N6C10D |  | Inductor_SMD:L_0402_1005Metric | https://lcsc.com/product-detail/Inductors-SMD_Murata-Electro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
52 | L4 | 1 | 15uH | MLZ2012M150W |  | Inductor_SMD:L_0805_2012Metric | https://www.digikey.com/short/zwbqfq
53 | L5 | 1 | 11nH | LQW15AN11NG00 |  | Inductor_SMD:L_0402_1005Metric | https://lcsc.com/product-detail/Inductors-SMD_Murata-Electro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
54 | L6 L7 | 2 | 47nH | LQW15AN47NJ00# |  | Inductor_SMD:L_0402_1005Metric | https://www.digikey.com/short/zwbq55
55 | L8 | 1 | 3nH | LQW15AN3N0B00 |  | Inductor_SMD:L_0402_1005Metric | https://lcsc.com/product-detail/Inductors-SMD_Murata-Electro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
56 | L2 L9 | 2 | 3.3nH | LQW15AN3N3C80D |  | Inductor_SMD:L_0402_1005Metric | https://www.digikey.com/short/zwbq2m
57 | N1 |  | BoLink-16174563 | DNM | S6L-303013 | node-lib-v1:BoLink_704025 | https://www.distrelec.nl/en/bolink-iot-enclosure-bolink-43-2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

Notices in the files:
Software/target/STM32WLxx_HAL_Driver/Src/stm32wlxx_hal_gpio.c:
© Copyright (c) 2020 STMicroelectronics.
All rights reserved.
This software component is licensed by ST under BSD 3-Clause license,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
(C) COPYRIGHT STMicroelectronics *****END OF FILE
